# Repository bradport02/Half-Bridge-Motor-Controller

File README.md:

# Half-Bridge Motor Controller — Driven ESAC

A custom half-bridge motor controller designed for a GreenPower electric race car, built for the Driven Electric Student Automotive Competition (ESAC) team. Designed to replace the team's off-the-shelf PORTER-10 controller, which limits continuous current to ~10-20 A.

**Status: design complete (schematic + 4-layer KiCad PCB), not yet fabricated or bench-tested.**

*3D render from KiCad — board has not yet been manufactured.*

## Purpose

Off-the-shelf controllers like the PORTER-10 are built for short current bursts and settle around 10-20 A continuous, which limits both acceleration off the line and sustained top speed. The goal was a controller capable of ~40 A continuous with a 120 A peak, giving the team a faster, more efficient motor drive and a platform that can be extended to regenerative braking in future.

## Target specification

- 120 A peak current draw
- ~40 A continuous draw
- 24 V system
- PWM input control
- On-board voltage regulation (24 V → 12 V → 5 V)

## How it works

The power stage is built around IRFB7440PbF N-channel MOSFETs (120 A rated), driven by a UCC21520 dual-channel gate driver. The UCC21520 takes PWM and control signals from a microcontroller and provides reinforced isolation between the low-voltage logic and the high-voltage power stage - protecting the control electronics from the transients typical of motor-drive environments. Its drive strength (4 A source / 6 A sink) is sized for fast, low-loss switching of the MOSFETs, and its programmable dead-time prevents shoot-through between high and low side.

Control interface:
- **PWM 1** — drive input
- **PWM 2** — regenerative braking input (architected for future use; not implemented in this revision. Both PWM inputs cannot be high simultaneously)
- **ENABLE** — logic-high enable

Signal isolation is handled by an ACSL-6400-50TE optocoupler for additional noise immunity.

## Connectors and I/O

- **Molex 43045-0806** — 8-pin signal input socket (PWM, enable, I²C, +12 V input)
- **Würth 7461098** — M8 metal lug connectors for battery and motor output, rated to 250 A

Two LM75 I²C temperature sensors monitor high-side and low-side MOSFET temperature, each with a programmable threshold that drives a status LED. The board has an onboard LED bank showing signal presence (PWM1/PWM2/Enable) and temperature-fault state at a glance.

## Voltage regulation

- **TSR-1-24120** steps 24 V down to 12 V, but only regulates correctly above ~15 V input.
- **UA78M05** regulates 12 V down to 5 V for logic.

**Known open item:** race telemetry shows battery voltage dropping below the TSR-1-24120's 15 V regulation floor during operation, which would drop the 12 V (and consequently 5 V) rail. A 12 V input pin is provided on the main connector as a workaround, but an external boost/always-available 12 V supply is the proposed fix and hasn't been implemented on this revision.

## PCB

Four-layer stack-up:
1. Power & signals
2. Continuous ground (noise isolation)
3. Ground & I²C
4. Power & signals

Specified for 2 oz copper on the outer layers for thermal dissipation, with extensive thermal vias. MOSFETs are oriented facing away from the board so they can be mounted to an external heatsink (as on the PORTER-10) rather than relying on the PCB alone for cooling.

Designed in KiCad across two schematic sheets — *Motor Controller* and *Power & Signals* — split for readability.

**This revision has no reverse-polarity protection.** This was a deliberate decision agreed with the ESAC team: the added complexity of full reverse-polarity protection at this current rating wasn't considered justified for this revision. BAT+ and BAT- are clearly marked on the silkscreen; correct wiring is required.

## Cost

Estimated production cost: **~£90/unit** (~£45 components, ~£45 PCB manufacture via JLCPCB). See the BOM for full component-level pricing.

## Future work

- Fabrication and bench testing of the current revision
- External 12 V supply to remove the low-battery-voltage regulation gap
- Regenerative braking implementation using the reserved PWM2 input

## Skills demonstrated

Power electronics design (MOSFET half-bridge, gate-drive isolation), 4-layer PCB design for high-current/thermal applications (KiCad), automotive/motorsport 12–24 V system design, I²C sensor integration, and BOM/cost engineering for a real production target.

## Author

Bradley Port — Designed for the Driven Electric Student Automotive Competition team.

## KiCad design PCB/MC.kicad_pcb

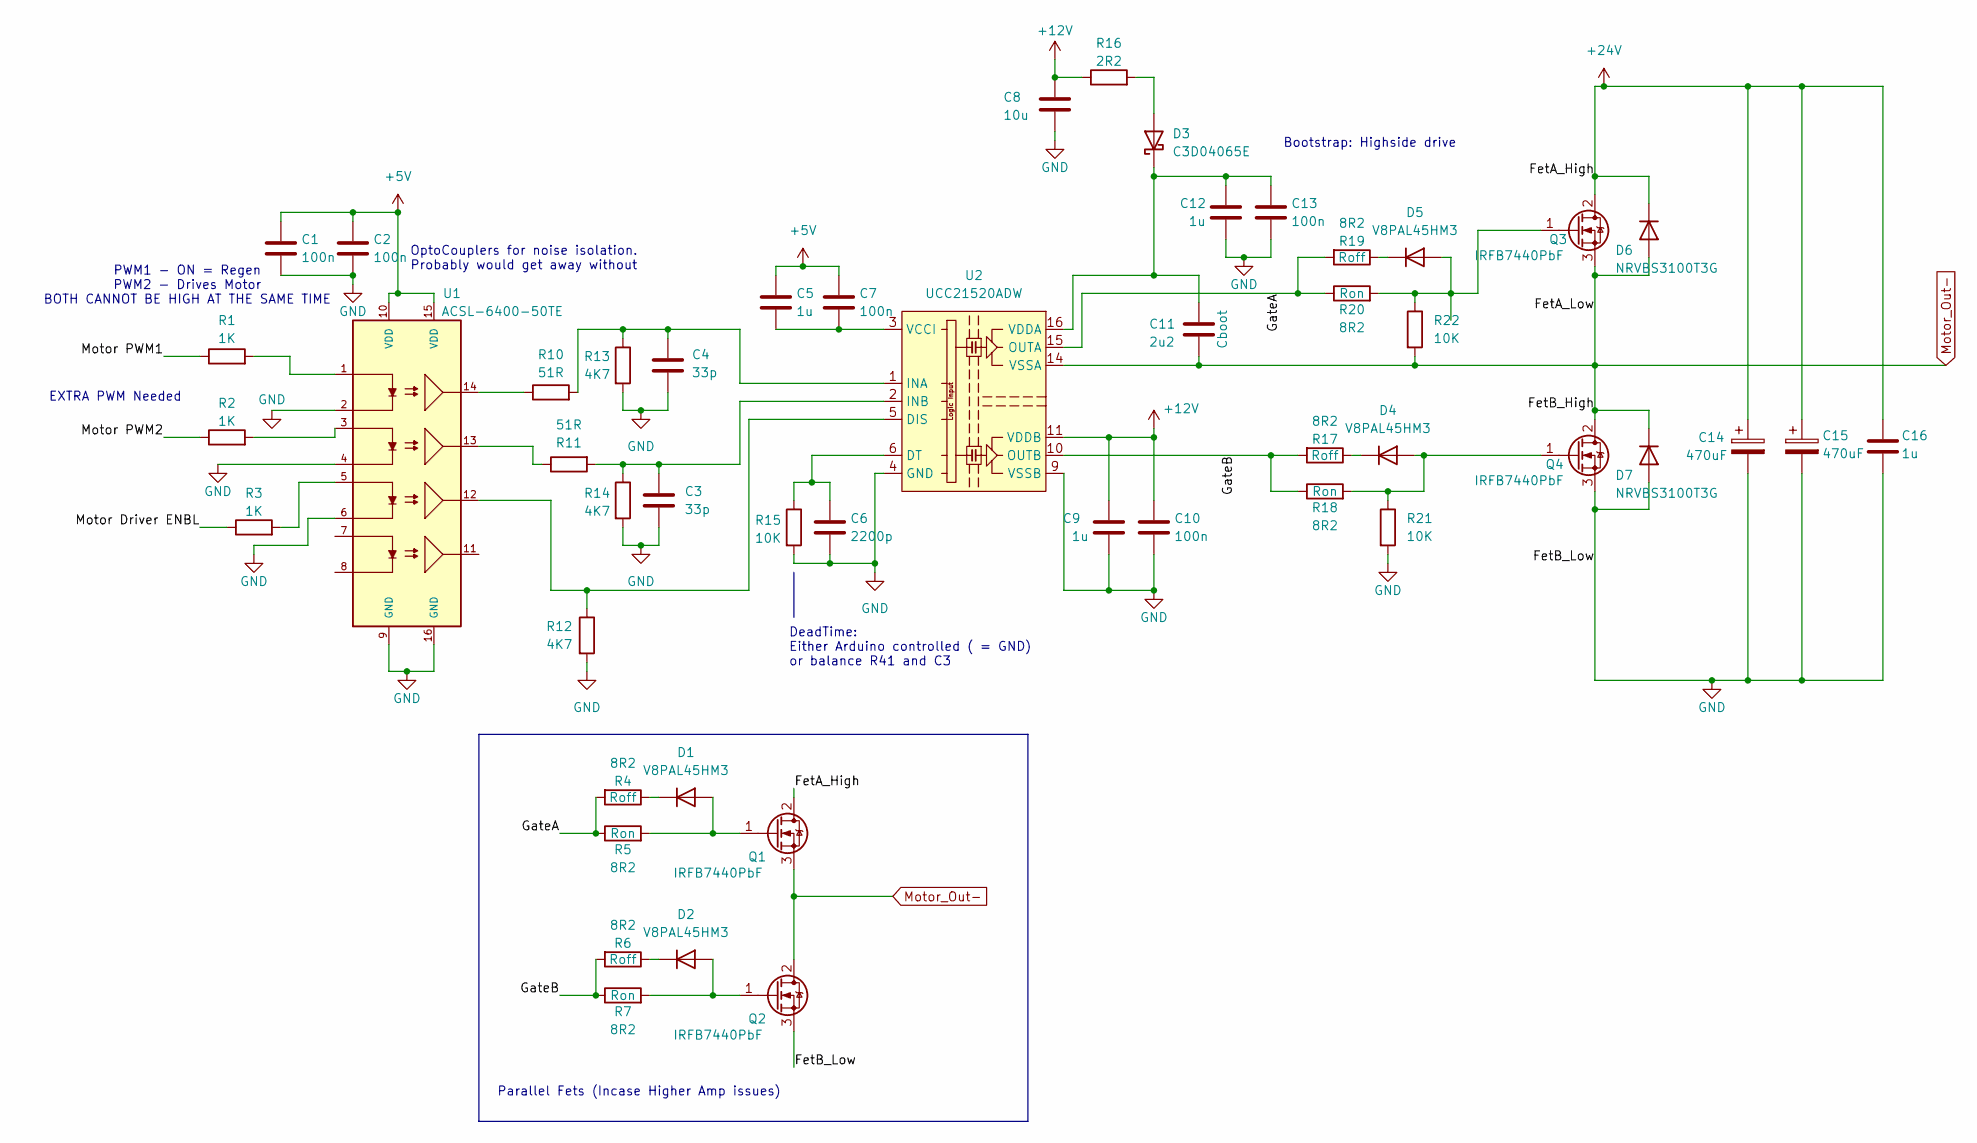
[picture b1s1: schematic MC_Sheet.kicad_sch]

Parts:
C1, C2, C7, C10, C13: 100n; C_0603_1608Metric_Pad1.08x0.95mm_HandSolder
C3, C4: 33p; C_0603_1608Metric_Pad1.08x0.95mm_HandSolder
C5, C9, C16: 1u; C_1206_3216Metric
C6: 2200p; C_0603_1608Metric_Pad1.08x0.95mm_HandSolder
C8: 10u; C_1206_3216Metric_Pad1.33x1.80mm_HandSolder
C11: 2u2; C_1206_3216Metric
C12: 1u; C_0603_1608Metric_Pad1.08x0.95mm_HandSolder
C14, C15: 470uF; CP_Elec_18x22
D1, D2, D4, D5: V8PAL45HM3; Vishay_SMPA
D3: C3D04065E; TO-252-2_TabPin1
D6, D7: NRVBS3100T3G; D_SMB-SMC_Universal_Handsoldering
Q1, Q2, Q3, Q4: IRFB7440PbF; TO-220-3_Horizontal_TabUp
R1, R2, R3: 1K; R_0603_1608Metric_Pad0.98x0.95mm_HandSolder
R4, R5, R6, R7, R17, R18, R19, R20: 8R2; R_2512_6332Metric_Pad1.40x3.35mm_HandSolder
R10, R11: 51R; R_0603_1608Metric_Pad0.98x0.95mm_HandSolder
R12, R13, R14: 4K7; R_0603_1608Metric_Pad0.98x0.95mm_HandSolder
R15, R21, R22: 10K; R_0603_1608Metric_Pad0.98x0.95mm_HandSolder
R16: 2R2; R_0603_1608Metric_Pad0.98x0.95mm_HandSolder
U1: ACSL-6400-50TE; SOIC127P599X172-16N; PARTREV August 21 2018
U2: UCC21520ADW; SOIC-16W_7.5x10.3mm_P1.27mm

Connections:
+5V: C1.1, C2.1, C5.1, C7.1, U1.10 (VDD), U1.15 (VDD); also elsewhere on the board
+12V: C8.1, C9.1, C10.1, R16.1, U2.11 (VDDB); also elsewhere on the board
+24V: C14.1, C15.1, C16.1, D6.1 (K), Q1.2 (D), Q3.2 (D); also elsewhere on the board
/Motor Controller/GateA: R4.2, R5.1, R19.2, R20.1, U2.15 (OUTA)
/Motor Controller/GateB: R6.2, R7.1, R17.2, R18.1, U2.10 (OUTB)
/Power & Signals/Motor Driver ENBL: R3.1; also elsewhere on the board
/Power & Signals/Motor PWM1: R1.1; also elsewhere on the board
/Power & Signals/Motor PWM2: R2.1; also elsewhere on the board
GND: C1.2, C2.2, C3.2, C4.2, C6.2, C8.2, C9.2, C10.2, C12.2, C13.2, C14.2, C15.2, C16.2, D7.2 (A), Q2.3 (S), Q4.3 (S), R12.2, R13.2, R14.2, R15.2, R21.2, U1.2, U1.4, U1.6, U1.9 (GND), U1.16 (GND), U2.4 (GND), U2.9 (VSSB); also elsewhere on the board
Motor_Out-: C11.2, D6.2 (A), D7.1 (K), Q1.3 (S), Q2.2 (D), Q3.3 (S), Q4.2 (D), R22.2, U2.14 (VSSA); also elsewhere on the board
unnamed: C5.2, C7.2, U2.3 (VCCI), U2.8 (VCCI)
unnamed: D1.2 (A), Q1.1 (G), R5.2
unnamed: D1.1 (K), R4.1
unnamed: D2.2 (A), Q2.1 (G), R7.2
unnamed: D2.1 (K), R6.1
unnamed: D3.2 (A), R16.2
unnamed: C11.1, C12.1, C13.1, D3.1 (K), U2.16 (VDDA)
unnamed: D4.2 (A), Q4.1 (G), R18.2, R21.1
unnamed: D4.1 (K), R17.1
unnamed: D5.2 (A), Q3.1 (G), R20.2, R22.1
unnamed: D5.1 (K), R19.1
unnamed: R1.2, U1.1
unnamed: R2.2, U1.3
unnamed: R3.2, U1.5
unnamed: R10.1, U1.14
unnamed: R11.1, U1.13
unnamed: R12.1, U1.12, U2.5 (DIS)
unnamed: C6.1, R15.1, U2.6 (DT)
unnamed: C4.1, R10.2, R13.1, U2.1 (INA)
unnamed: C3.1, R11.2, R14.1, U2.2 (INB)

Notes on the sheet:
Bootstrap: Highside drive
EXTRA PWM Needed
OptoCouplers for noise isolation. Probably would get away without
Parallel Fets (Incase Higher Amp issues)
PWM1 - ON = Regen PWM2 - Drives Motor BOTH CANNOT BE HIGH AT THE SAME TIME
DeadTime: Either Arduino controlled ( = GND) or balance R41 and C3

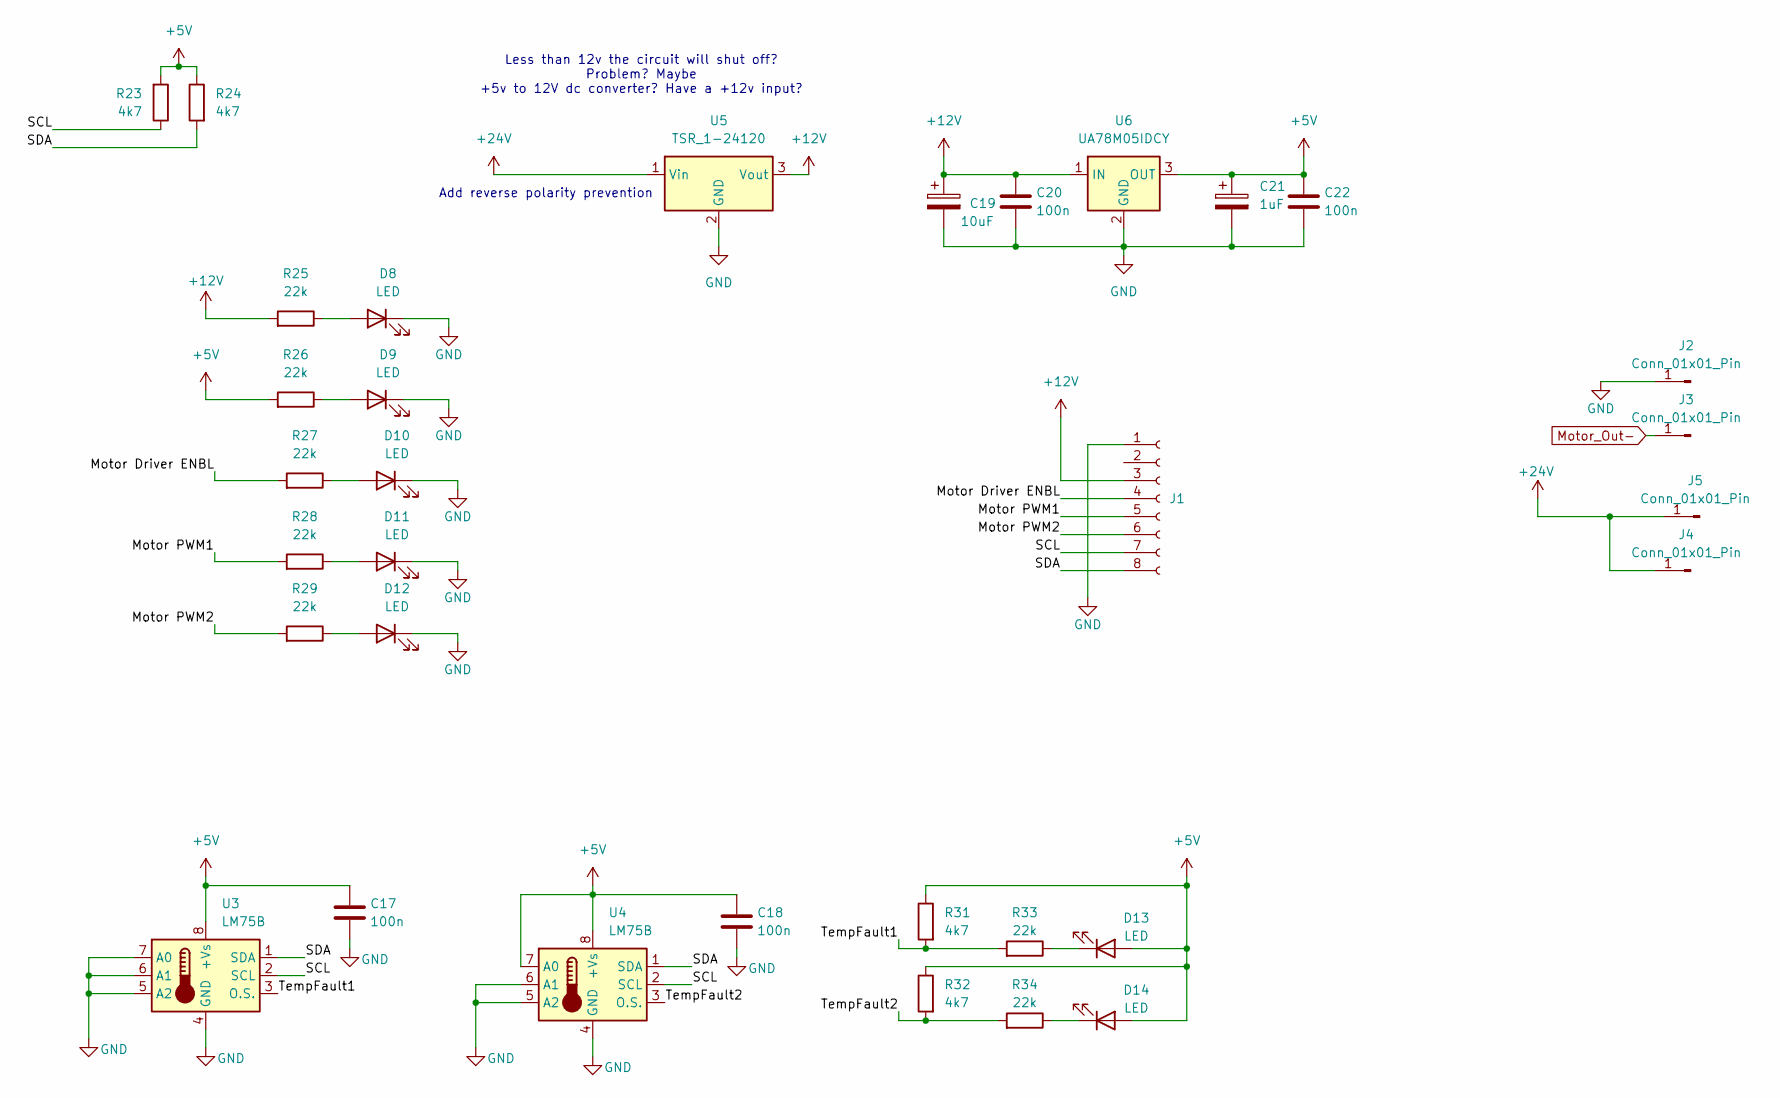
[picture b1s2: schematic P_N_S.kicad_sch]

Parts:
C17, C18, C20, C22: 100n; C_0603_1608Metric_Pad1.08x0.95mm_HandSolder
C19: 10uF; CP_Elec_6.3x5.8
C21: 1uF; CP_Elec_4x5.8
D8, D9, D10, D11, D12, D13, D14: LED; LED_0603_1608Metric
J1: Conn_01x08_Socket; 43045-08YY_060708_1
J2, J3, J4, J5: Conn_01x01_Pin; 7461098
R23, R24, R31, R32: 4k7; R_0603_1608Metric_Pad0.98x0.95mm_HandSolder
R25, R26, R27, R28, R29, R33, R34: 22k; R_0603_1608Metric_Pad0.98x0.95mm_HandSolder
U3, U4: LM75B; SOIC-8_3.9x4.9mm_P1.27mm
U5: TSR_1-24120; Converter_DCDC_TRACO_TSR-1_THT
U6: UA78M05IDCY; SOT-223-3_TabPin2

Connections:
+5V: C17.1, C18.1, C21.1, C22.1, D13.2 (A), D14.2 (A), R23.2, R24.1, R26.2, R31.1, R32.1, U3.8 (+Vs), U4.7 (A0), U4.8 (+Vs), U6.3 (OUT); also elsewhere on the board
+12V: C19.1, C20.1, J1.3, R25.2, U5.3 (Vout), U6.1 (IN); also elsewhere on the board
+24V: J4.1, J5.1, U5.1 (Vin); also elsewhere on the board
/Power & Signals/Motor Driver ENBL: J1.4, R27.2; also elsewhere on the board
/Power & Signals/Motor PWM1: J1.5, R28.2; also elsewhere on the board
/Power & Signals/Motor PWM2: J1.6, R29.2; also elsewhere on the board
/Power & Signals/SCL: J1.7, R23.1, U3.2 (SCL), U4.2 (SCL)
/Power & Signals/SDA: J1.8, R24.2, U3.1 (SDA), U4.1 (SDA)
/Power & Signals/TempFault1: R31.2, R33.2, U3.3 (O.S.)
/Power & Signals/TempFault2: R32.2, R34.2, U4.3 (O.S.)
GND: C17.2, C18.2, C19.2, C20.2, C21.2, C22.2, D8.1 (K), D9.1 (K), D10.1 (K), D11.1 (K), D12.1 (K), J1.1, J2.1, U3.4 (GND), U3.5 (A2), U3.6 (A1), U3.7 (A0), U4.4 (GND), U4.5 (A2), U4.6 (A1), U5.2 (GND), U6.2 (GND); also elsewhere on the board
Motor_Out-: J3.1; also elsewhere on the board
unnamed: D8.2 (A), R25.1
unnamed: D9.2 (A), R26.1
unnamed: D10.2 (A), R27.1
unnamed: D11.2 (A), R28.1
unnamed: D12.2 (A), R29.1
unnamed: D13.1 (K), R33.1
unnamed: D14.1 (K), R34.1

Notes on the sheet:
Less than 12v the circuit will shut off? Problem? Maybe +5v to 12V dc converter? Have a +12v input?
Add reverse polarity prevention

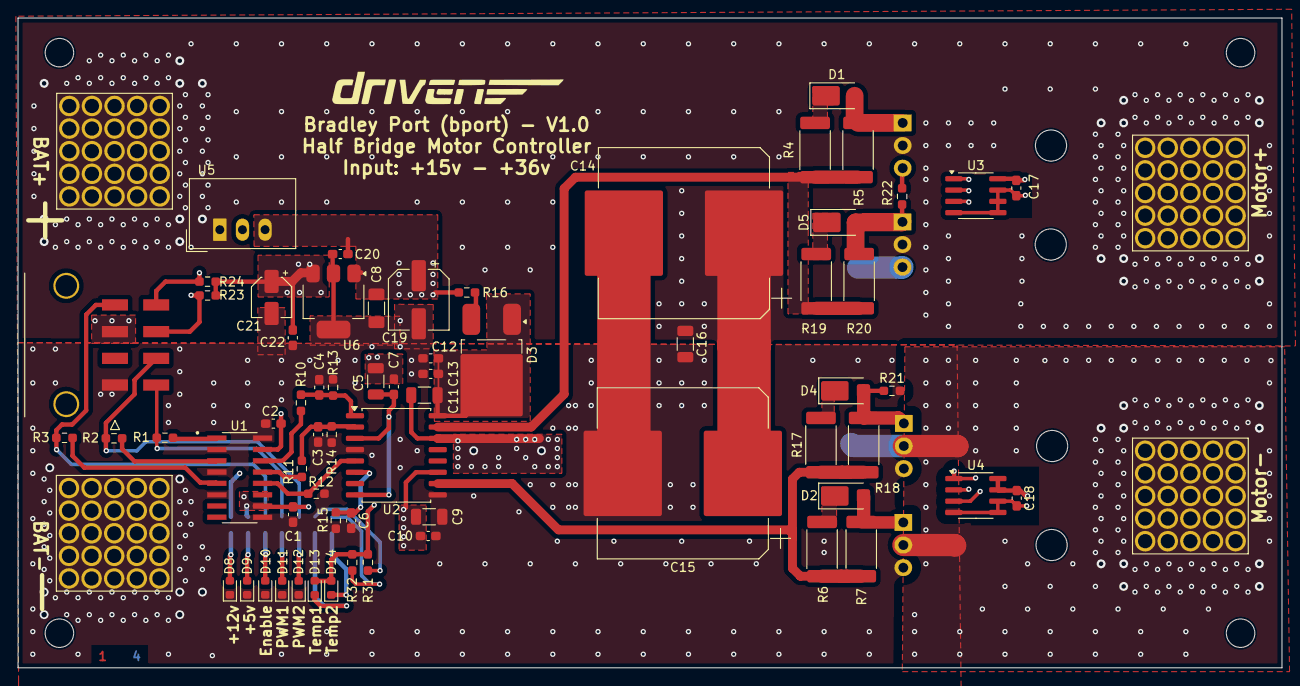
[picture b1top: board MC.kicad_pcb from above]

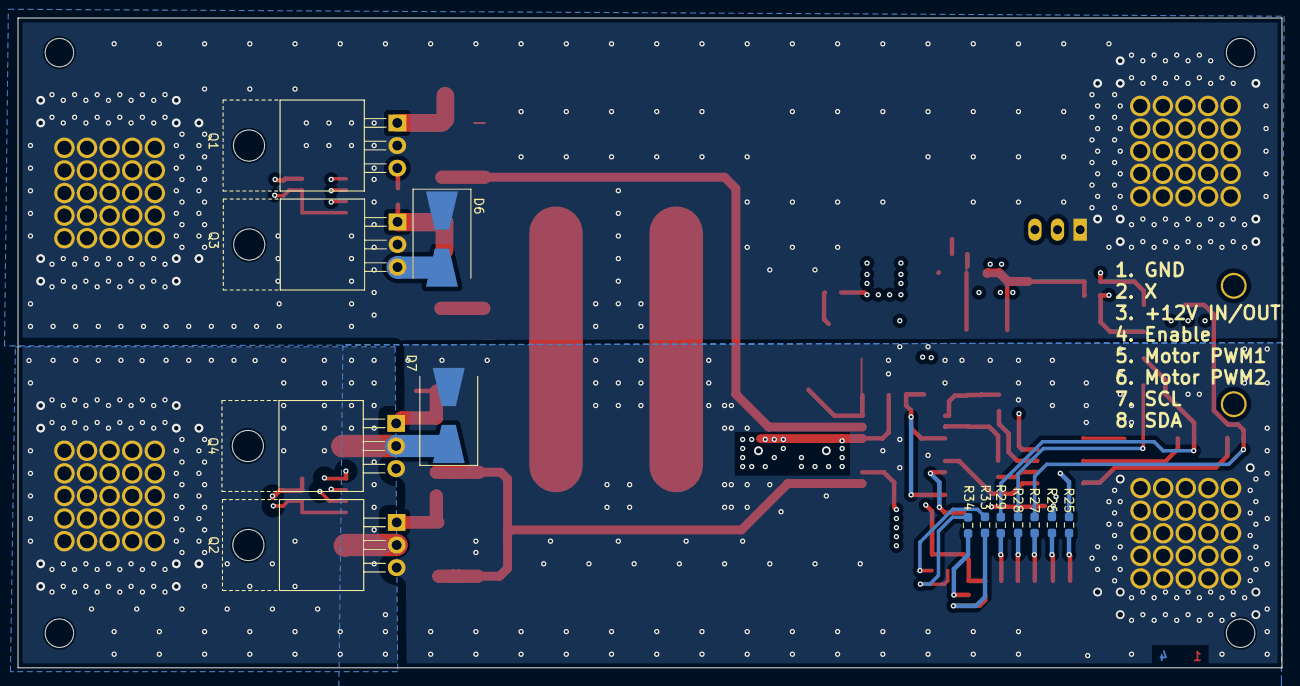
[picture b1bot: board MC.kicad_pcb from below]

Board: 4 copper layers, 142.0 x 73.0 mm, 82 parts (13 on the bottom side), 41 nets.
